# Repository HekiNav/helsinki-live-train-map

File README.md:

# Helsinki Live LED Train Map

A real-time PCB map of the Helsinki Region train network, powered by an ESP32-C3 microcontroller. Train movements are displayed using addressable RGB LEDs, with live data fetched over Wi-Fi.

---

## Table of Contents

- [Helsinki Live LED Train Map](#helsinki-live-led-train-map)
  - [Table of Contents](#table-of-contents)
  - [Features](#features)
  - [Hardware](#hardware)
  - [Design](#design)
  - [Software / Firmware](#software--firmware)
  - [Getting Started](#getting-started)
  - [Web Installer](#web-installer)
  - [Web Simulator](#web-simulator)
  - [Stand](#stand)
  - [Server](#server)
  - [Links](#links)
  - [Contributing](#contributing)
  - [License](#license)

---

## Features

- **Real-time Train Tracking:** Displays the approximate locations of trains on the HSL and VR commuter network.
- **Addressable LEDs:** ~290 WS2812B-compatible RGB LEDs (1.6x1.5mm) for a vibrant display.
- **Wi-Fi Connectivity:** ESP32-C3's built-in Wi-Fi fetches live train data.
- **Custom PCB:** Designed for JLCPCB manufacturing limits.
- **Open Source:** Hardware and firmware are open source.

---

## Hardware

- **Microcontroller:** Expressif ESP32-C3FH4 (RISC-V, 160 MHz, 4 MB Flash, QFN32)
- **Level shifter:** Texas Instruments SN74LVC4245APWR (3.3V to 5V)
- **LEDs:** ~290 x XingLight XL-1615RGBC-WS2812B (1.6mm x 1.5mm)
- **PCB:** 249mm x 71.5mm, JLCPCB-friendly
- **Antenna:** On-board PCB antenna ([TI CC2430DB design](https://www.ti.com/lit/ug/swru125/swru125.pdf))
- **Ports:** Two USB Type-C ports for redundancy

---

## Design

### Rail diagram design

Inspiration for the layout was taken from the VR rail map used on commuter trains (above the doors). 

**Each LED represents a double-track line**
- 8-tracked sections (4 LEDs wide):
   1. Helsinki-Pasila
- Quad-tracked sections (2 express commuter & intercity, 2 slower commuter):
   1. Pasila-Leppävaara-(Kauklahti [Under construction])
   2. Pasila-Kerava

- Exceptions to single-track lines: 
   1. Tavastila-Kotkan satama
   2. Siuntio-Hanko

### Technical design

- Designed in **KiCad V9.0** using [JLCPCB KiCad Library](https://github.com/CDFER/jlcpcb-kicad-library)
- **View Online:** [Interactive PCB Layout (Kicanvas)](https://kicanvas.org/?github=https%3A%2F%2Fgithub.com%2FHekiNav%2Fhelsinki-live-train-map%2Ftree%2Fmain%2FPCB)
- **Source Files:** `/PCB` directory
### Schematic
Led chains are located on other pages

---

## Software / Firmware

NOTE! Software and firmware have been moved to [another repo](https://github.com/HekiNav/legacy-ltm-firmware)

The ESP32-C3 firmware is responsible for:

1. Connecting to Wi-Fi
2. Fetching live train data from the API
3. Processing data to determine train locations
4. Controlling WS2812B LED chains to display train positions
5. Handling button inputs and status LEDs
6. Hosting a web page for configuration

---

## Getting Started

1. **Flash the Firmware:**
   - Use the [Web Installer](#web-installer) (recommended, no drivers needed)
   - Or flash manually using PlatformIO (`Firmware/` directory)
2. **Connect to Wi-Fi:**
   - On first boot, use the web installer interface to configure Wi-Fi credentials. They are saved locally on the device.
3. **Power the Board:**
   - Use a 5V USB-C power supply capable of at least ~1A (~2A recommended for compatibility with higher brightness settings).
4. **Configure in the :**
   - Visit the IP address of your device (shown in Web Installer)
   - Configure options like tails, brightness and mode 
5. **Enjoy the Live Train Map!**

### Status LEDs

The top (🔌) power led is hardwired to the power rail

The middle and bottom status leds are controlled by the MCU

| LED | Light | Meaning |
|-----|-------|---------|
| top (🔌)    |🟩 green | The board is powered
| top (🔌)    |⬛ none  | The board is not powered
| top (🔌)    |🟥 red   | This shouldn't happen although it's techically possible if there's severe issues in the pcb
|||
| middle (ᯤ)  |🟩 green            | Connected to the API
| middle (ᯤ)  |🟩 green \(blinking\) | Mode change pending
| middle (ᯤ)  |⬛ none             | Connecting to the API
| middle (ᯤ)  |🟥 red              | Failed to connect to API
|||
| bottom (🌐)  |🟩 green \(blinking\) | Connecting to wifi
| bottom (🌐)  |🟩 green            | Connected to wifi
| bottom (🌐)  |⬛ none             | Failed to boot
| bottom (🌐)  |🟥 red              | Failed to connect to wifi

### Map Modes

There are 4(+1) map modes on the device. You can switch the mode by pressing the map (🗺️) button or by going to the control panel.

#### Lines (default)
- Shows commuter trains by line
- Only commuter trains
- Some colors are reused on lines that do not intersect

| Color                         | Line     | |
|-------------------------------|----------|-|
|$${\color{#f00}\Huge\text{■}}$$| Z        | |
|$${\color{#f80}\Huge\text{■}}$$| A        | |
|$${\color{#ff0}\Huge\text{■}}$$| E,O      | |
|$${\color{#0f0}\Huge\text{■}}$$| P,G      | |
|$${\color{#0ff}\Huge\text{■}}$$| M,I      | |
|$${\color{#00f}\Huge\text{■}}$$| K        | |
|$${\color{#80f}\Huge\text{■}}$$| Y,L,H    | |
|$${\color{#f0f}\Huge\text{■}}$$| U        | |
|$${\color{#f08}\Huge\text{■}}$$| D,T,R    | |
|$${\color{#fff}\Huge\text{■}}$$| V, Other | Look up on [juliadata.fi](https://juliadata.fi/map/view?mode=trains#8.86/60.3487/25.1733)|

\* V is used in transfer services

#### Delay
- Shows the delay state of trains
- Only commuter trains

| Color                         | Delay (min) | Description          |
|-------------------------------|-------------|----------------------|
|$${\color{#0ff}\Huge\text{■}}$$| < 0         | Ahead of schedule    |  
|$${\color{#0f0}\Huge\text{■}}$$| 0 - 2       | On time              |
|$${\color{#ff0}\Huge\text{■}}$$| 2 - 10      | Mild delay           |
|$${\color{#f00}\Huge\text{■}}$$| > 20        | Severe delay         |
|$${\color{#f0f}\Huge\text{■}}$$| -           | Unknown delay amount |

#### Composition
- Shows the locomotives/EMUs of trains
- ALL trains shown (incl. InterCity, freight)

| Color                         | Loco                                     | Description                                |
|-------------------------------|------------------------------------------|--------------------------------------------|
| EMUs                          |                                          |                                            |
|$${\color{#f00}\Huge\text{■}}$$| [Sm2](https://fi.wikipedia.org/wiki/Sm2) | Commuter, old                              |
|$${\color{#0f0}\Huge\text{■}}$$| [Sm3](https://fi.wikipedia.org/wiki/Sm3) | Pendolino (IC)                             |
|$${\color{#ff0}\Huge\text{■}}$$| [Sm4](https://fi.wikipedia.org/wiki/Sm4) | Commuter, longer distances                 |
|$${\color{#80f}\Huge\text{■}}$$| [Sm5](https://fi.wikipedia.org/wiki/Sm5) | Commuter, shorter distances                |
|$${\color{#f0f}\Huge\text{■}}$$| [Sm6](https://fi.wikipedia.org/wiki/Sm6) | Allegro (IC)                               |
|$${\color{#f80}\Huge\text{■}}$$| [Sm7](https://fi.wikipedia.org/wiki/Sm7) | Commuter, not in regular service yet       |
| Locos                         |                                          |                                            |
|$${\color{#0ff}\Huge\text{■}}$$| [Sr2](https://fi.wikipedia.org/wiki/Sr2) | IC locomotive                              |
|$${\color{#00f}\Huge\text{■}}$$| [Sr3](https://fi.wikipedia.org/wiki/Sr3) | Newer IC locomotive                        |
| Other                         |                                          |                                            |
|$${\color{#f08}\Huge\text{■}}$$| N/A                                      | No composition found (most likely freight) |
|$${\color{#fff}\Huge\text{■}}$$| Other                                    | Other locomotive with no color defined (Look up on [juliadata.fi](https://juliadata.fi/map/view?mode=trains#8.86/60.3487/25.1733)) |

#### Train types
- Shows the types of trains
- ALL trains shown (incl. InterCity, freight)

| Color                         | Code                  | Description                                |
|-------------------------------|-----------------------|--------------------------------------------|
|$${\color{#f00}\Huge\text{■}}$$| IC                    | Double-decker intercity trains             |
|$${\color{#f80}\Huge\text{■}}$$| VET                   | Locomotive train                           |
|$${\color{#f80}\Huge\text{■}}$$| MUS, MUV              | Heritage train                             |
|$${\color{#0f0}\Huge\text{■}}$$| S                     | Pendolino train                            |
|$${\color{#00f}\Huge\text{■}}$$| T                     | Freight train                              |
|$${\color{#80f}\Huge\text{■}}$$| HL                    | Commuter train                             |
|$${\color{#f0f}\Huge\text{■}}$$| HV                    | Commuter train transfer                    |
|$${\color{#f08}\Huge\text{■}}$$| PAR, PAI, VEV, W, SAA | Shunting                                   |
|$${\color{#fff}\Huge\text{■}}$$| Other                 | Other train type with no color defined (Look up on [juliadata.fi](https://juliadata.fi/map/view?mode=trains#8.86/60.3487/25.1733)) |

#### Test
- Shows the types of LEDs

| Color                         | Type         | Description                          | Technical logic                                                    |
|-------------------------------|--------------|--------------------------------------|--------------------------------------------------------------------|
|$${\color{#ff0}\Huge\text{■}}$$| Station      | All services stop                    | Train has arrived, but not departed                                |
|$${\color{#f00}\Huge\text{■}}$$| Stop         | Express services skip                | Same as station                                                    |
|$${\color{#0f0}\Huge\text{■}}$$| Between      | Single LED between stops/stations    | Train left previous, not arrived at next                           |
|$${\color{#0ff}\Huge\text{■}}$$| MultiBetween | Multiple LEDs between stops/stations | Same as between, but exact position is appoximated using timetable |

#### Disruptions
- Shows disruptions for stations and trains

| Color                         | Disruption                |
|-------------------------------|---------------------------|
|$${\color{#f00}\Huge\text{■}}$$| Cancellation              |
|$${\color{#f80}\Huge\text{■}}$$| Infrastructure disruption |
|$${\color{#ff0}\Huge\text{■}}$$| Other disruption          |
|$${\color{#0f0}\Huge\text{■}}$$| Track work                |
|$${\color{#0ff}\Huge\text{■}}$$| Private train             |
|$${\color{#00f}\Huge\text{■}}$$| Replacement service       |
|$${\color{#80f}\Huge\text{■}}$$| Missing/replaced wagon(s) |
|$${\color{#fff}\Huge\text{■}}$$| Unclassified              |

---

## Web Installer

Easily flash the latest firmware to your ESP32-C3 using your browser:

[Open the Helsinki LED Train Map Web Installer](https://hekinav.github.io/ltm-firmware/led-rails.html)

- Works with Chrome, Edge, or any Web Serial-compatible browser
- Follow on-screen instructions to connect and flash your device

---

## Web Simulator

View the map without having the physical pcb:

[Open the Helsinki LED Train Map Web Simulator](https://hekinav.github.io/ltm-firmware/sim.html)

- Use the map mode button to switch display modes, just like on the real thing
- Works with most modern browsers
- Fetches data from the API

---
## Stand and other 3D Models

A 3d-printable stand to hold up the board. Files are located in `/3D Models`

---

## Server

Processes train running data from [digitraffic](https://rata.digitraffic.fi/). Documentation for the train API is available at https://www.digitraffic.fi/rautatieliikenne. Most of it is only available in finnish.

### Main packages:
- express: API handling
- mqtt: Listening to MQTT train messages 
- node-sqlite & sqlite3: Database for cached train compositions and stats
- node-cron: Cron jobs for recaching data and cleaning the database

The api is tunneled to [ltm.hekinav.dev](https://ltm.hekinav.dev/).

### Running locally

Install npm packages

`npm install`

Start the api in dev mode (watches files) (uses port 3001 by default)

`npm run dev`

### Production

Compile TS to JS

`npm run build`

Start the server

`npm run start` or in PM2 `pm2 start ./ecosystem.config.cjs`

---

## Links

- [Web Installer](https://hekinav.github.io/ltm-firmware//led-rails.html)
- [Web Simulator](https://hekinav.github.io/ltm-firmware//sim.html)
- [Interactive PCB Viewer](https://kicanvas.org/?github=https%3A%2F%2Fgithub.com%2FHekiNav%2Fhelsinki-live-train-map%2Ftree%2Fmain%2FPCB)
- [JLCPCB KiCad Library](https://github.com/CDFER/jlcpcb-kicad-library)

---

## Contributing

Contributions are welcome! Open an issue or submit a pull request for improvements, bug fixes, or feature suggestions.

---

## Attributions

Thanks to [Chris (CDFER)](https://github.com/CDFER/) for the base and support of this project. Check out his store with multiple LED Rail Maps at [keastudios.co.nz](https://keastudios.co.nz/)

## License

This project is released under the MIT license.

© 2025 Chris Dirks & Unto Ahti

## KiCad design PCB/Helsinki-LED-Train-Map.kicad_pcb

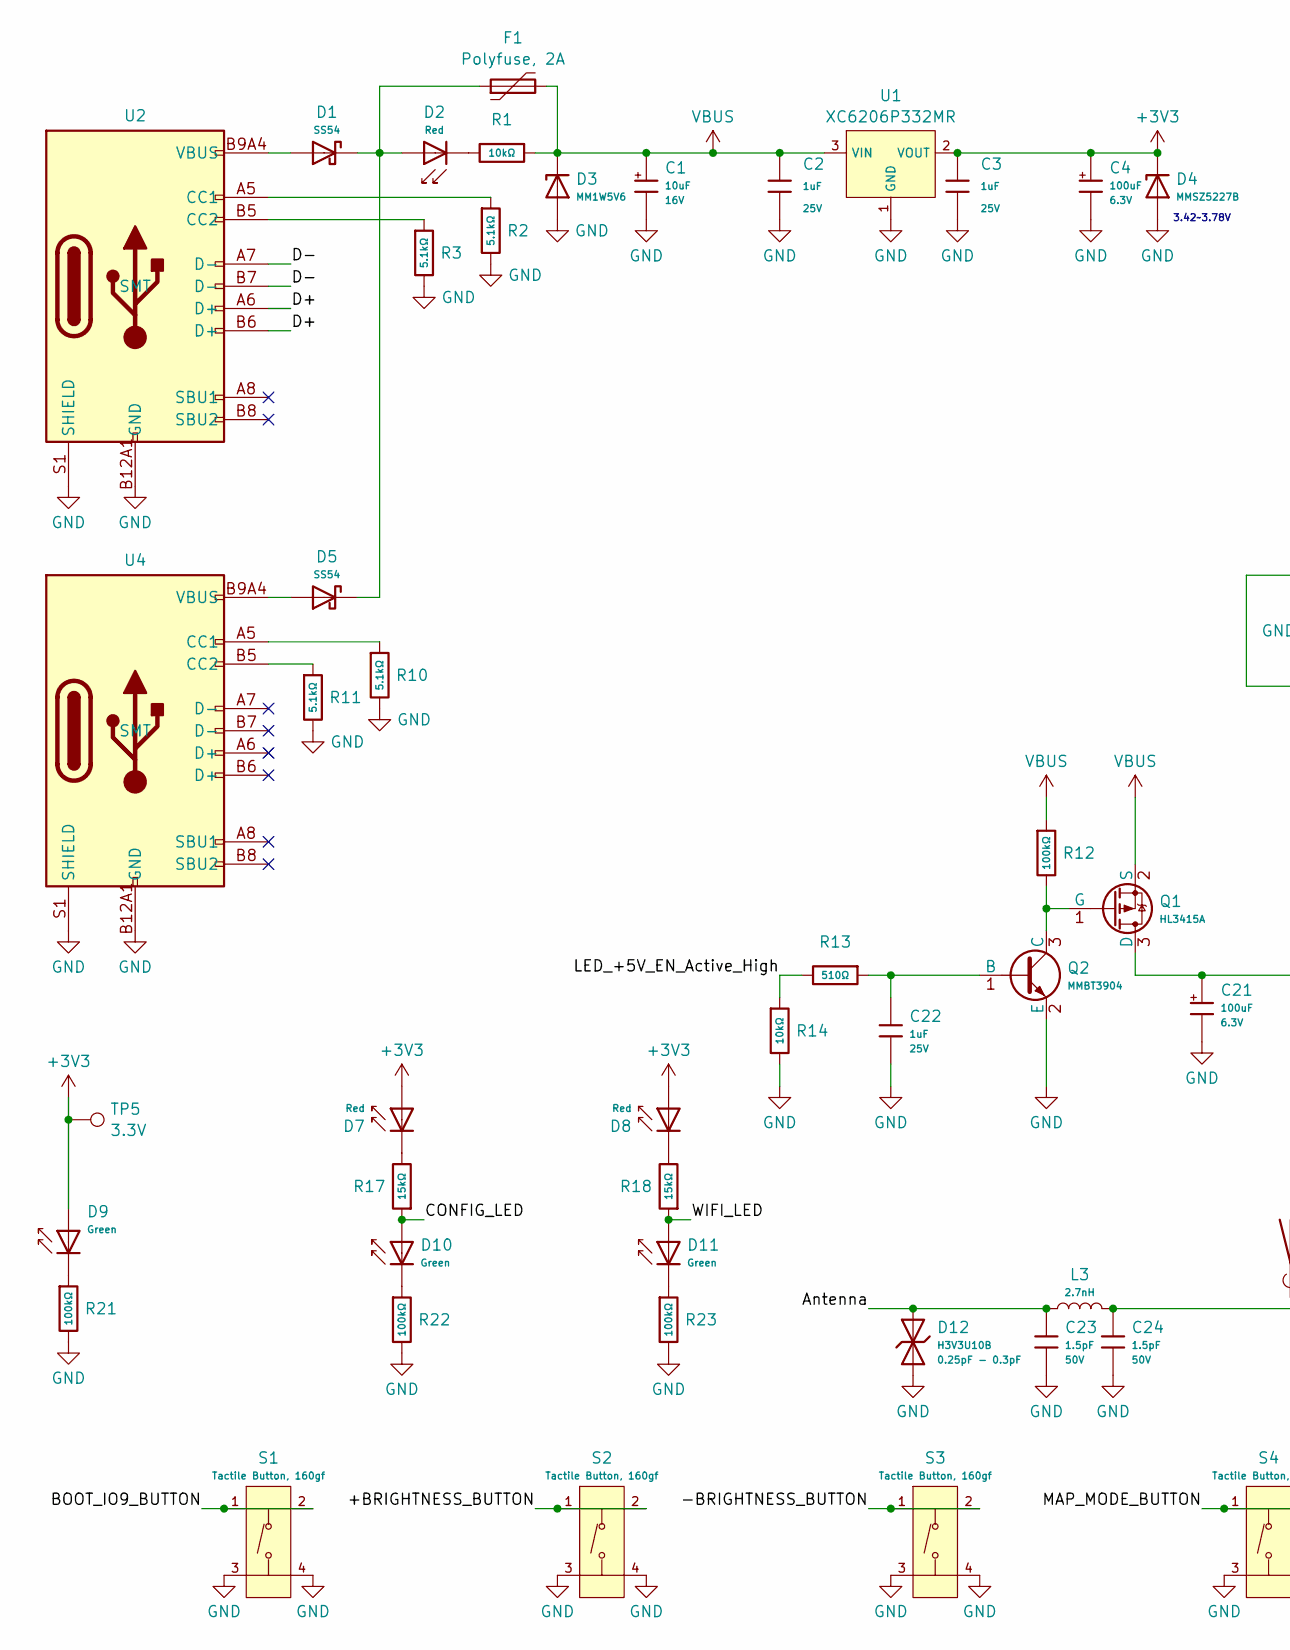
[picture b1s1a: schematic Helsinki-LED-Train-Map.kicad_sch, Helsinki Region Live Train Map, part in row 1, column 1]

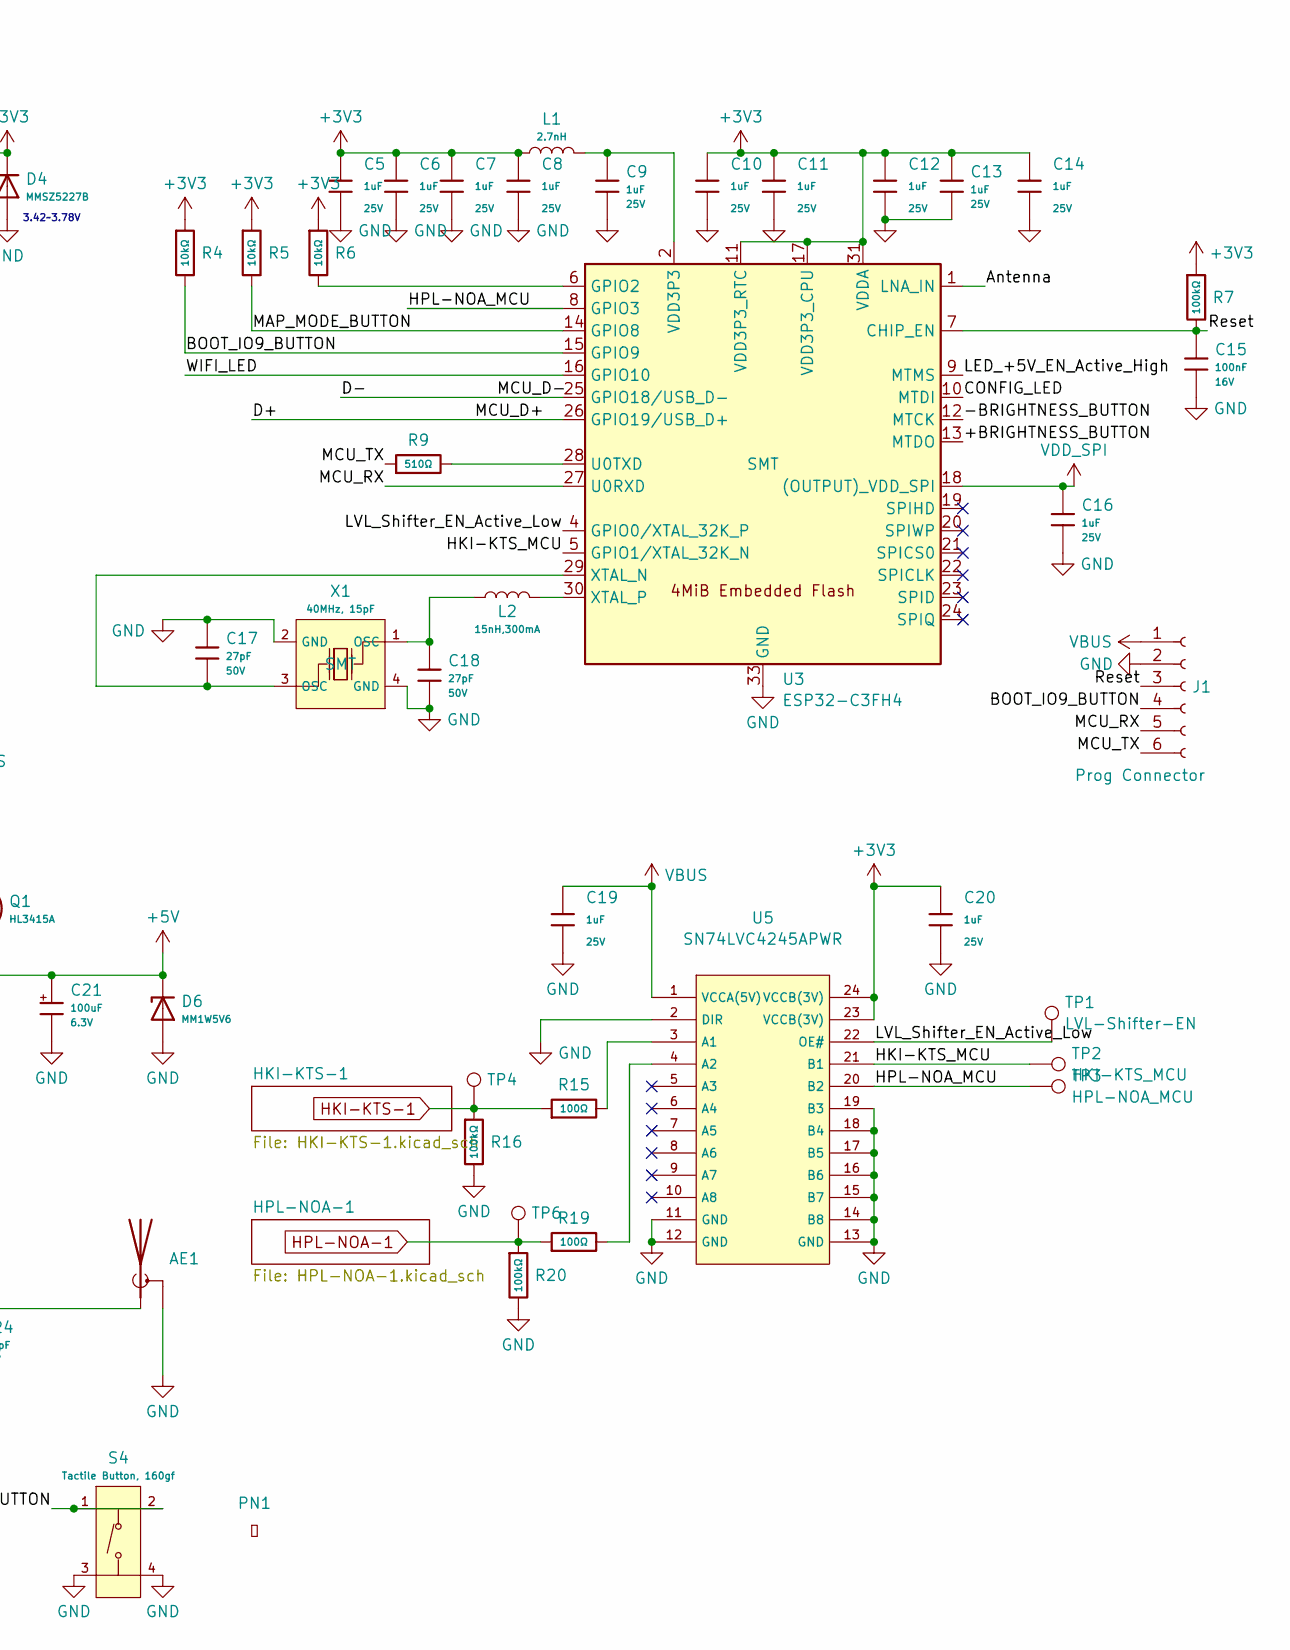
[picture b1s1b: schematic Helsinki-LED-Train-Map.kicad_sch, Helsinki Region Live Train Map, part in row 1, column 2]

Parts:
AE1: Antenna_Shield; Inverted_F_Antenna_2.4Ghz_1.0mmPCB_TI_CC2430DB.pretty
C1: 10uF; C_CASE-A-3216-18(mm); Tolerance ±10%; Rated Voltage 16V; Part TAJA106K016RNJ; LCSC C7171
C2, C3, C5, C6, C7, C8, C9, C10, C11, C12, C13, C14, C16, C19, C20, C22: 1uF; C_0402; Voltage Rated 25V; Tolerance ±10%; Part CL05A105KA5NQNC; LCSC C52923
C4, C21: 100uF; C_CASE-B-3528-21(mm); Tolerance ±10%; Rated Voltage 6.3V; Part TAJB107K006RNJ; LCSC C16133
C15: 100nF; C_0402; Voltage Rated 16V; Tolerance ±10%; Part CL05B104KO5NNNC; LCSC C1525
C17, C18: 27pF; C_0402; Voltage Rated 50V; Tolerance ±5%; Part 0402CG270J500NT; LCSC C1557
C23, C24: 1.5pF; C_0402; Voltage Rated 50V; Part 0402CG1R5C500NT; LCSC C1552
D1, D5: SS54; D_SMA; Forward Voltage (Vf@If) 550mV@5A; Reverse Voltage (Vr) 40V; Part SS54; LCSC C22452
D2, D7, D8: Red; D_0805; Forward Voltage (VF) 1.6V~2.6V; Part NCD0805R1; LCSC C84256
D3, D6: MM1W5V6; D_SOD-123; Part MM1W5V6; LCSC C22435086
D4: MMSZ5227B; D_SOD-123; Part MMSZ5227B; LCSC C22395553
D9, D10, D11: Green; D_0805; Part KT-0805G; LCSC C2297
D12: H3V3U10B; D_DFN1006-2L; Part H3V3U10B; LCSC C20615782
F1: Polyfuse, 2A; Fuse_1206_3216Metric; LCSC C6165195
J1: Prog Connector
L1, L3: 2.7nH; L_0402; Part LQG15HS2N7S02D; LCSC C77108
L2: 15nH,300mA; L_0402; Tolerance ±5%; Part SDCL1005C15NJTDF; LCSC C27143
PN1: Part_Num_JLCPCB
Q1: HL3415A; Q_SOT-23; Part HL3415A; LCSC C28646270
Q2: MMBT3904; Q_SOT-23; Part MMBT3904; LCSC C7420353
R1, R4, R5, R6, R14: 10kΩ; R_0402; Overload Voltage (Max) 50V; Tolerance ±1%; Part 0402WGF1002TCE; LCSC C25744
R2, R3, R10, R11: 5.1kΩ; R_0402; Overload Voltage (Max) 50V; Tolerance ±1%; Part 0402WGF5101TCE; LCSC C25905
R7, R12, R16, R20, R21, R22, R23: 100kΩ; R_0402; Overload Voltage (Max) 50V; Tolerance ±1%; Part 0402WGF1003TCE; LCSC C25741
R9, R13: 510Ω; R_0402; Overload Voltage (Max) 50V; Tolerance ±1%; Part 0402WGF5100TCE; LCSC C25123
R15, R19: 100Ω; R_0402; Overload Voltage (Max) 50V; Tolerance ±1%; Part 0402WGF1000TCE; LCSC C25076
R17, R18: 15kΩ; R_0402; Overload Voltage (Max) 50V; Tolerance ±1%; Part 0402WGF1502TCE; LCSC C25756
S1, S2, S3, S4: Tactile Button, 160gf; SW-SMD_4P-L5.1-W5.1-P3.70-LS6.5-TL-2; Voltage Rating (Dc) 12V; Part TS-1187A-B-A-B; LCSC C318884
TP1: LVL-Shifter-EN; TestPoint_Pad_D1.0mm
TP2: HKI-KTS_MCU; TestPoint_Pad_D1.0mm
TP3: HPL-NOA_MCU; TestPoint_Pad_D1.0mm
TP4: STRAND-MNK_LED; TestPoint_Pad_D1.0mm
TP5: 3.3V; TestPoint_Pad_D1.0mm
TP6: NAL-NIMT_LED; TestPoint_Pad_D1.0mm
U1: XC6206P332MR; SOT-23-3_L2.9-W1.6-P1.90-LS2.8-BR; Output Voltage 3.3V; Dropout Voltage 680mV@(100mA); Part XC6206P332MR-G; LCSC C5446
U2, U4: Connector, USB-TYPE-C-16P; TYPE-C-SMD_HX-TYPE-C-16PIN; Part USB-TYPE-C-019; LCSC C2927039
U3: ESP32-C3FH4; QFN-32-1EP_5x5mm_P0.5mm_EP3.7x3.7mm_ThermalVias; Part ESP32-C3FH4; LCSC C2858491
U5: SN74LVC4245APWR; TSSOP-24_4.4x7.8mm_P0.65mm; Part SN74LVC4245APWR; LCSC C7859
X1: 40MHz, 15pF; OSC-SMD_4P-L3.2-W2.5-BL_SIT8008BI; Part X322540MPB4SI; LCSC C9010

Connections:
+3V3: C3.1, C4.1, C5.1, C6.1, C7.1, C8.1, C10.1, C11.1, C12.1, C13.1, C14.1, C20.1, D4.1, D7.2, D8.2, D9.2, L1.1, R4.1, R5.1, R6.1, R7.1, TP5.1, U1.2 (VOUT), U3.11 (VDD3P3_RTC), U3.17 (VDD3P3_CPU), U3.31 (VDDA), U3.32 (VDDA), U5.23 (VCCB(3V)), U5.24 (VCCB(3V))
+5V: C21.1, D6.1, Q1.3 (D); also elsewhere on the board
/+BRIGHTNESS_BUTTON: S2.1 (A), S2.2 (B), U3.13 (MTDO)
/-BRIGHTNESS_BUTTON: S3.1 (A), S3.2 (B), U3.12 (MTCK)
/Antenna: C23.1, D12.2, L3.1, U3.1 (LNA_IN)
/BOOT_IO9_BUTTON: J1.4, R4.2, S1.1 (A), S1.2 (B), U3.15 (GPIO9)
/CONFIG_LED: D10.2, R17.1, U3.10 (MTDI)
/D+: U2.A6 (D+), U2.B6 (D+), U3.26 (GPIO19/USB_D+)
/D-: U2.A7 (D-), U2.B7 (D-), U3.25 (GPIO18/USB_D-)
/HKI-KTS_MCU: TP2.1, U3.5 (GPIO1/XTAL_32K_N), U5.21 (B1)
/HPL-NOA_MCU: TP3.1, U3.8 (GPIO3), U5.20 (B2)
/LED_+5V_EN_Active_High: R13.2, R14.1, U3.9 (MTMS)
/LVL_Shifter_EN_Active_Low: TP1.1, U3.4 (GPIO0/XTAL_32K_P), U5.22 (OE#)
/MAP_MODE_BUTTON: R5.2, S4.1 (A), S4.2 (B), U3.14 (GPIO8)
/MCU_RX: J1.5, U3.27 (U0RXD)
/MCU_TX: J1.6, R9.1
/Reset: C15.1, J1.3, R7.2, U3.7 (CHIP_EN)
/WIFI_LED: D11.2, R18.1, U3.16 (GPIO10)
GND: AE1.2 (Shield), C1.2, C2.2, C3.2, C4.2, C5.2, C6.2, C7.2, C8.2, C9.2, C10.2, C11.2, C12.2, C13.2, C14.2, C15.2, C16.2, C17.1, C18.2, C19.2, C20.2, C21.2, C22.2, C23.2, C24.2, D3.2, D4.2, D6.2, D12.1, J1.2, Q2.2 (E), R2.2, R3.2, R10.2, R11.2, R14.2, R16.2, R20.2, R21.2, R22.2, R23.2, S1.3 (C), S1.4 (D), S2.3 (C), S2.4 (D), S3.3 (C), S3.4 (D), S4.3 (C), S4.4 (D), U1.1 (GND), U2.A12B1 (GND), U2.B12A1 (GND), U2.S1 (SHIELD), U3.33 (GND), U4.A12B1 (GND), U4.B12A1 (GND), U4.S1 (SHIELD), U5.2 (DIR), U5.11 (GND), U5.12 (GND), U5.13 (GND), U5.14 (B8), U5.15 (B7), U5.16 (B6), U5.17 (B5), U5.18 (B4), U5.19 (B3), X1.2 (GND), X1.4 (GND); also elsewhere on the board
HKI-KTS-1: R15.1, R16.1, TP4.1; also elsewhere on the board
HPL-NOA-1: R19.1, R20.1, TP6.1; also elsewhere on the board
unnamed: AE1.1 (A), C24.1, L3.2
unnamed: C9.1, L1.2, U3.2 (VDD3P3), U3.3 (VDD3P3)
unnamed: C18.1, L2.1, X1.1 (OSC)
unnamed: D1.1, D2.2, D5.1, F1.1
unnamed: D1.2, U2.A9B4 (VBUS), U2.B9A4 (VBUS)
unnamed: D2.1, R1.2
unnamed: D5.2, U4.A9B4 (VBUS), U4.B9A4 (VBUS)
unnamed: D7.1, R17.2
unnamed: D8.1, R18.2
unnamed: D9.1, R21.1
unnamed: D10.1, R22.1
unnamed: D11.1, R23.1
unnamed: Q1.1 (G), Q2.3 (C), R12.2
unnamed: C22.1, Q2.1 (B), R13.1
unnamed: R2.1, U2.A5 (CC1)
unnamed: R3.1, U2.B5 (CC2)
unnamed: R6.2, U3.6 (GPIO2)
unnamed: R9.2, U3.28 (U0TXD)
unnamed: C17.2, U3.29 (XTAL_N), X1.3 (OSC)
unnamed: L2.2, U3.30 (XTAL_P)
unnamed: R10.1, U4.A5 (CC1)
unnamed: R11.1, U4.B5 (CC2)
unnamed: R15.2, U5.3 (A1)
unnamed: R19.2, U5.4 (A2)
VBUS: C1.1, C2.1, C19.1, D3.1, F1.2, J1.1, Q1.2 (S), R1.1, R12.1, U1.3 (VIN), U5.1 (VCCA(5V))
VDD_SPI: C16.1, U3.18 ((OUTPUT)_VDD_SPI)

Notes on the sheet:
3.42~3.78V

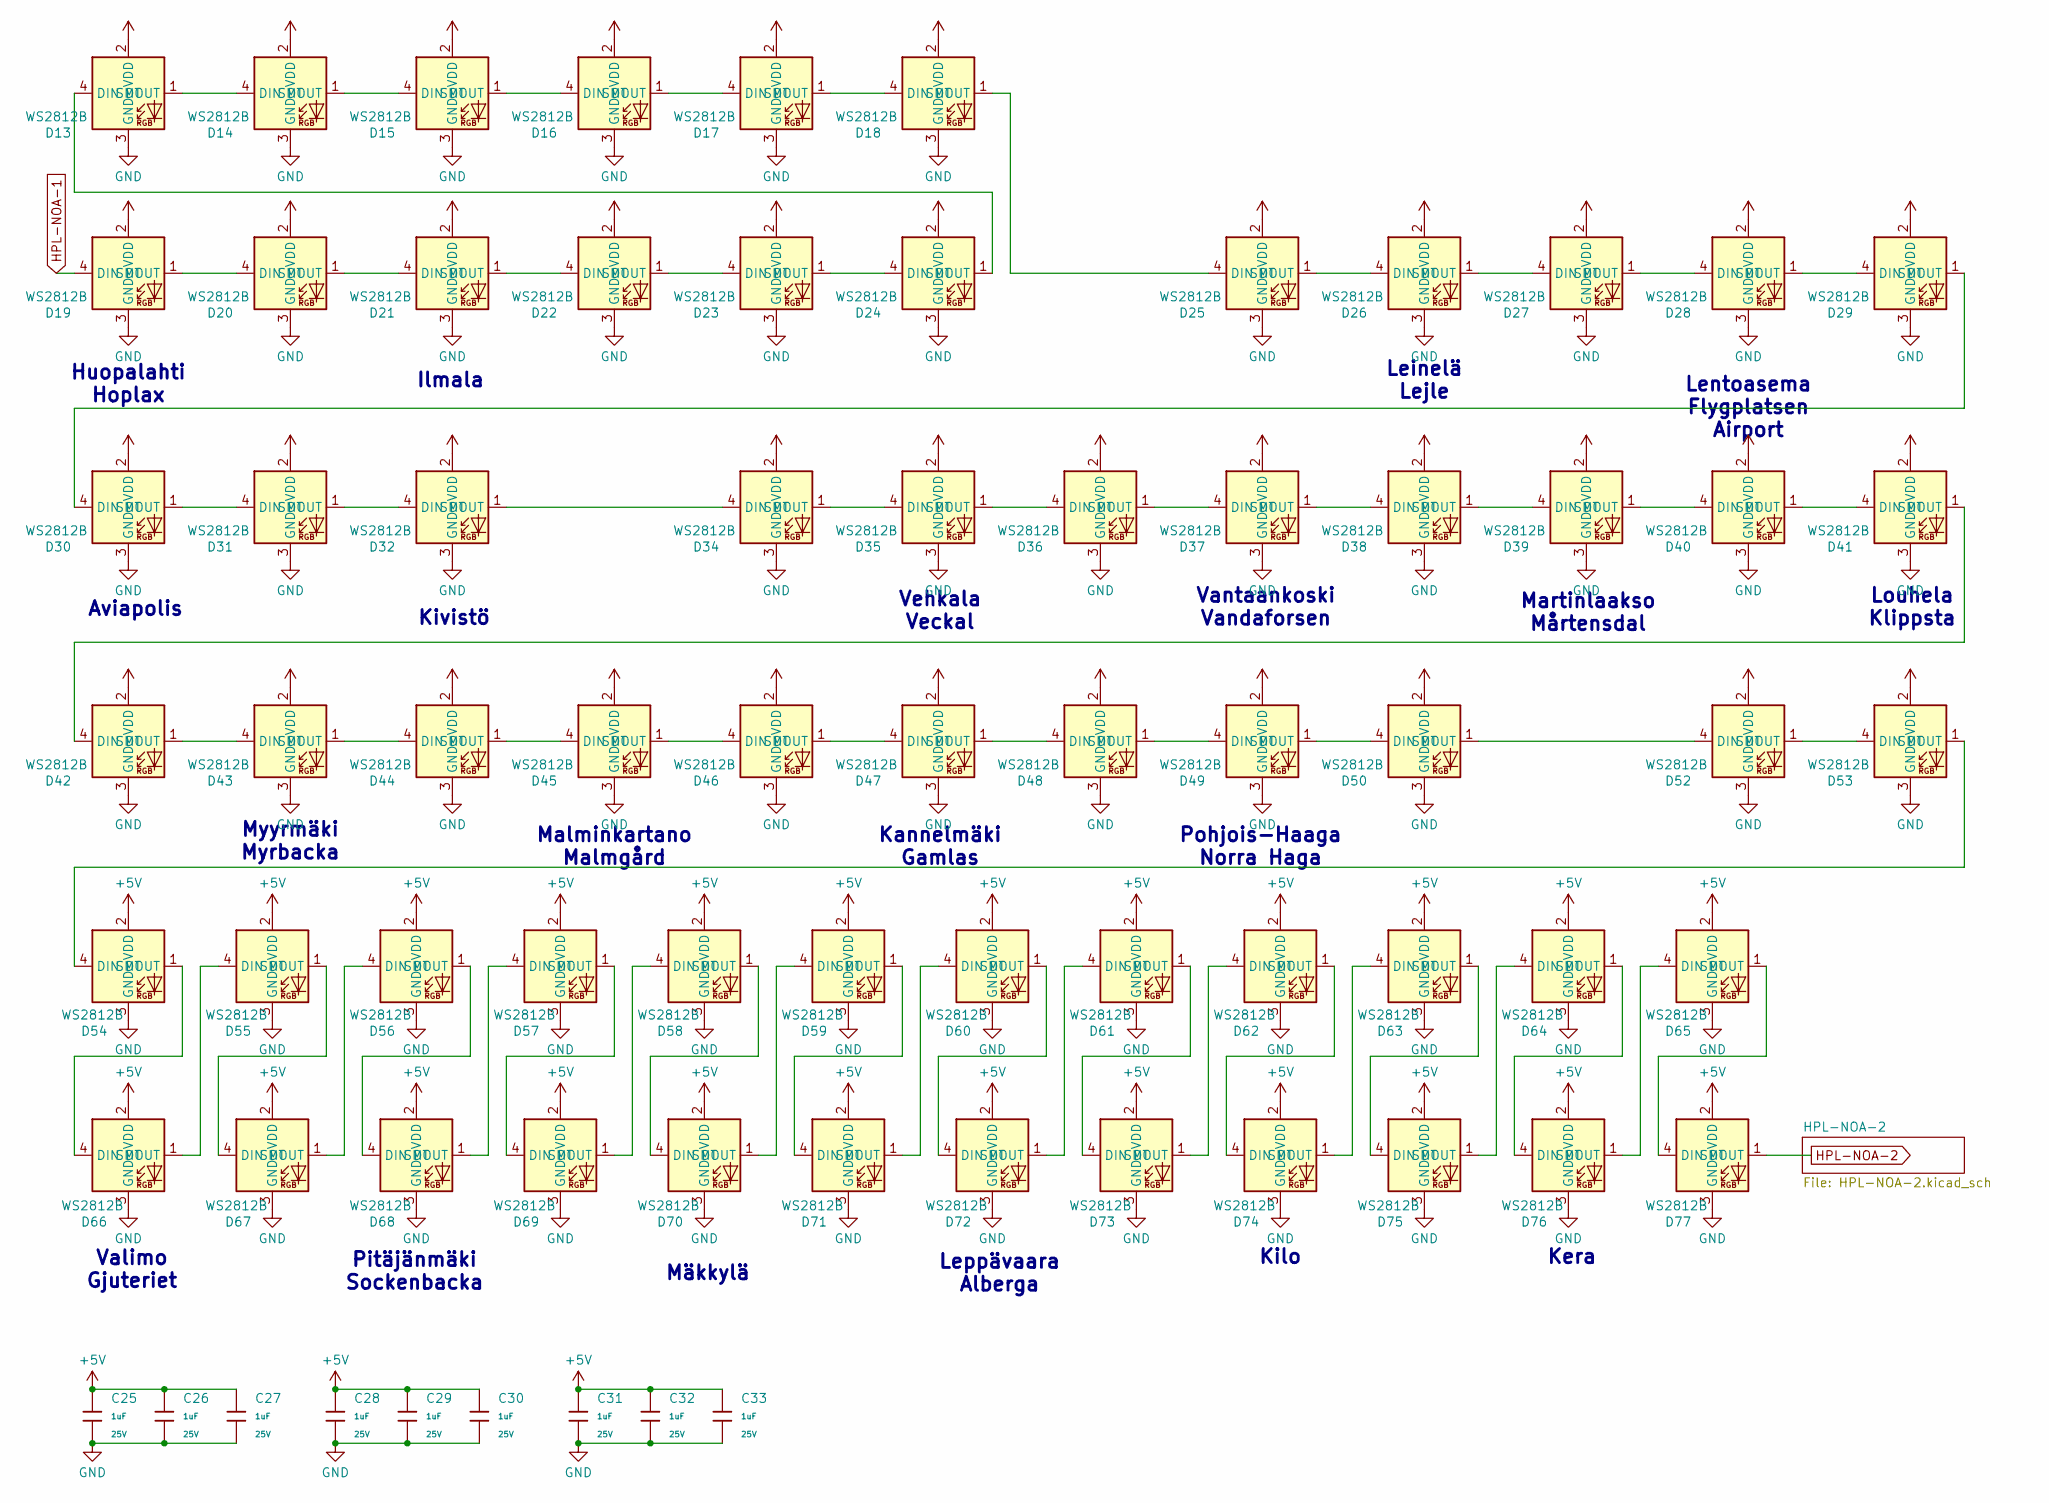
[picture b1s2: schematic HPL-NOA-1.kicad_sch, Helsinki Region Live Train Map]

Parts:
C25, C26, C27, C28, C29, C30, C31, C32, C33: 1uF; C_0402; Voltage Rated 25V; Tolerance ±10%; Part CL05A105KA5NQNC; LCSC C52923
D13, D14, D15, D16, D17, D18, D19, D20, D21, D22, D23, D24, D25, D26, D27, D28, D29, D30, D31, D32, D34, D35, D36, D37, D38, D39, D40, D41, D42, D43, D44, D45, D46, D47, D48, D49, D50, D52, D53, D54, D55, D56, D57, D58, D59, D60, D61, D62, D63, D64, D65, D66, D67, D68, D69, D70, D71, D72, D73, D74, D75, D76, D77: WS2812B; LED-SMD_4P-L1.6-W1.5_XL-1615RGBC-WS2812B; Part XL-1615RGBC-WS2812B; LCSC C5349954

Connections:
+5V: C25.1, C26.1, C27.1, C28.1, C29.1, C30.1, C31.1, C32.1, C33.1, D13.2 (VDD), D14.2 (VDD), D15.2 (VDD), D16.2 (VDD), D17.2 (VDD), D18.2 (VDD), D19.2 (VDD), D20.2 (VDD), D21.2 (VDD), D22.2 (VDD), D23.2 (VDD), D24.2 (VDD), D25.2 (VDD), D26.2 (VDD), D27.2 (VDD), D28.2 (VDD), D29.2 (VDD), D30.2 (VDD), D31.2 (VDD), D32.2 (VDD), D34.2 (VDD), D35.2 (VDD), D36.2 (VDD), D37.2 (VDD), D38.2 (VDD), D39.2 (VDD), D40.2 (VDD), D41.2 (VDD), D42.2 (VDD), D43.2 (VDD), D44.2 (VDD), D45.2 (VDD), D46.2 (VDD), D47.2 (VDD), D48.2 (VDD), D49.2 (VDD), D50.2 (VDD), D52.2 (VDD), D53.2 (VDD), D54.2 (VDD), D55.2 (VDD), D56.2 (VDD), D57.2 (VDD), D58.2 (VDD), D59.2 (VDD), D60.2 (VDD), D61.2 (VDD), D62.2 (VDD), D63.2 (VDD), D64.2 (VDD), D65.2 (VDD), D66.2 (VDD), D67.2 (VDD), D68.2 (VDD), D69.2 (VDD), D70.2 (VDD), D71.2 (VDD), D72.2 (VDD), D73.2 (VDD), D74.2 (VDD), D75.2 (VDD), D76.2 (VDD), D77.2 (VDD); also elsewhere on the board
GND: C25.2, C26.2, C27.2, C28.2, C29.2, C30.2, C31.2, C32.2, C33.2, D13.3 (GND), D14.3 (GND), D15.3 (GND), D16.3 (GND), D17.3 (GND), D18.3 (GND), D19.3 (GND), D20.3 (GND), D21.3 (GND), D22.3 (GND), D23.3 (GND), D24.3 (GND), D25.3 (GND), D26.3 (GND), D27.3 (GND), D28.3 (GND), D29.3 (GND), D30.3 (GND), D31.3 (GND), D32.3 (GND), D34.3 (GND), D35.3 (GND), D36.3 (GND), D37.3 (GND), D38.3 (GND), D39.3 (GND), D40.3 (GND), D41.3 (GND), D42.3 (GND), D43.3 (GND), D44.3 (GND), D45.3 (GND), D46.3 (GND), D47.3 (GND), D48.3 (GND), D49.3 (GND), D50.3 (GND), D52.3 (GND), D53.3 (GND), D54.3 (GND), D55.3 (GND), D56.3 (GND), D57.3 (GND), D58.3 (GND), D59.3 (GND), D60.3 (GND), D61.3 (GND), D62.3 (GND), D63.3 (GND), D64.3 (GND), D65.3 (GND), D66.3 (GND), D67.3 (GND), D68.3 (GND), D69.3 (GND), D70.3 (GND), D71.3 (GND), D72.3 (GND), D73.3 (GND), D74.3 (GND), D75.3 (GND), D76.3 (GND), D77.3 (GND); also elsewhere on the board
HPL-NOA-1: D19.4 (DIN); also elsewhere on the board
HPL-NOA-2: D77.1 (DOUT); also elsewhere on the board
unnamed: D13.4 (DIN), D24.1 (DOUT)
unnamed: D13.1 (DOUT), D14.4 (DIN)
unnamed: D14.1 (DOUT), D15.4 (DIN)
unnamed: D15.1 (DOUT), D16.4 (DIN)
unnamed: D16.1 (DOUT), D17.4 (DIN)
unnamed: D17.1 (DOUT), D18.4 (DIN)
unnamed: D18.1 (DOUT), D25.4 (DIN)
unnamed: D19.1 (DOUT), D20.4 (DIN)
unnamed: D20.1 (DOUT), D21.4 (DIN)
unnamed: D21.1 (DOUT), D22.4 (DIN)
unnamed: D22.1 (DOUT), D23.4 (DIN)
unnamed: D23.1 (DOUT), D24.4 (DIN)
unnamed: D25.1 (DOUT), D26.4 (DIN)
unnamed: D26.1 (DOUT), D27.4 (DIN)
unnamed: D27.1 (DOUT), D28.4 (DIN)
unnamed: D28.1 (DOUT), D29.4 (DIN)
unnamed: D29.1 (DOUT), D30.4 (DIN)
unnamed: D30.1 (DOUT), D31.4 (DIN)
unnamed: D31.1 (DOUT), D32.4 (DIN)
unnamed: D32.1 (DOUT), D34.4 (DIN)
unnamed: D34.1 (DOUT), D35.4 (DIN)
unnamed: D35.1 (DOUT), D36.4 (DIN)
unnamed: D36.1 (DOUT), D37.4 (DIN)
unnamed: D37.1 (DOUT), D38.4 (DIN)
unnamed: D38.1 (DOUT), D39.4 (DIN)
unnamed: D39.1 (DOUT), D40.4 (DIN)
unnamed: D40.1 (DOUT), D41.4 (DIN)
unnamed: D41.1 (DOUT), D42.4 (DIN)
unnamed: D42.1 (DOUT), D43.4 (DIN)
unnamed: D43.1 (DOUT), D44.4 (DIN)
unnamed: D44.1 (DOUT), D45.4 (DIN)
unnamed: D45.1 (DOUT), D46.4 (DIN)
unnamed: D46.1 (DOUT), D47.4 (DIN)
unnamed: D47.1 (DOUT), D48.4 (DIN)
unnamed: D48.1 (DOUT), D49.4 (DIN)
unnamed: D49.1 (DOUT), D50.4 (DIN)
unnamed: D50.1 (DOUT), D52.4 (DIN)
unnamed: D52.1 (DOUT), D53.4 (DIN)
unnamed: D53.1 (DOUT), D54.4 (DIN)
unnamed: D54.1 (DOUT), D66.4 (DIN)
unnamed: D55.4 (DIN), D66.1 (DOUT)
unnamed: D55.1 (DOUT), D67.4 (DIN)
unnamed: D56.4 (DIN), D67.1 (DOUT)
unnamed: D56.1 (DOUT), D68.4 (DIN)
unnamed: D57.4 (DIN), D68.1 (DOUT)
unnamed: D57.1 (DOUT), D69.4 (DIN)
unnamed: D58.4 (DIN), D69.1 (DOUT)
unnamed: D58.1 (DOUT), D70.4 (DIN)
unnamed: D59.4 (DIN), D70.1 (DOUT)
unnamed: D59.1 (DOUT), D71.4 (DIN)
unnamed: D60.4 (DIN), D71.1 (DOUT)
unnamed: D60.1 (DOUT), D72.4 (DIN)
unnamed: D61.4 (DIN), D72.1 (DOUT)
unnamed: D61.1 (DOUT), D73.4 (DIN)
unnamed: D62.4 (DIN), D73.1 (DOUT)
unnamed: D62.1 (DOUT), D74.4 (DIN)
unnamed: D63.4 (DIN), D74.1 (DOUT)
unnamed: D63.1 (DOUT), D75.4 (DIN)
unnamed: D64.4 (DIN), D75.1 (DOUT)
unnamed: D64.1 (DOUT), D76.4 (DIN)
unnamed: D65.4 (DIN), D76.1 (DOUT)
unnamed: D65.1 (DOUT), D77.4 (DIN)

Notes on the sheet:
Kannelmäki Gamlas
Leinelä Lejle
Mäkkylä
Aviapolis
Martinlaakso Mårtensdal
Pitäjänmäki Sockenbacka
Louhela Klippsta
Valimo Gjuteriet
Lentoasema Flygplatsen Airport
Malminkartano Malmgård
Pohjois-Haaga Norra Haga
Vantaankoski Vandaforsen
Kera
Myyrmäki Myrbacka
Huopalahti Hoplax
Kilo
Vehkala Veckal
Leppävaara Alberga
Ilmala
Kivistö

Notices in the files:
PCB/HKI-KTS-1.kicad_sch:
©Chris Dirks & Unto Ahti
PCB/Helsinki-LED-Train-Map.kicad_pcb:
©Chris Dirks
